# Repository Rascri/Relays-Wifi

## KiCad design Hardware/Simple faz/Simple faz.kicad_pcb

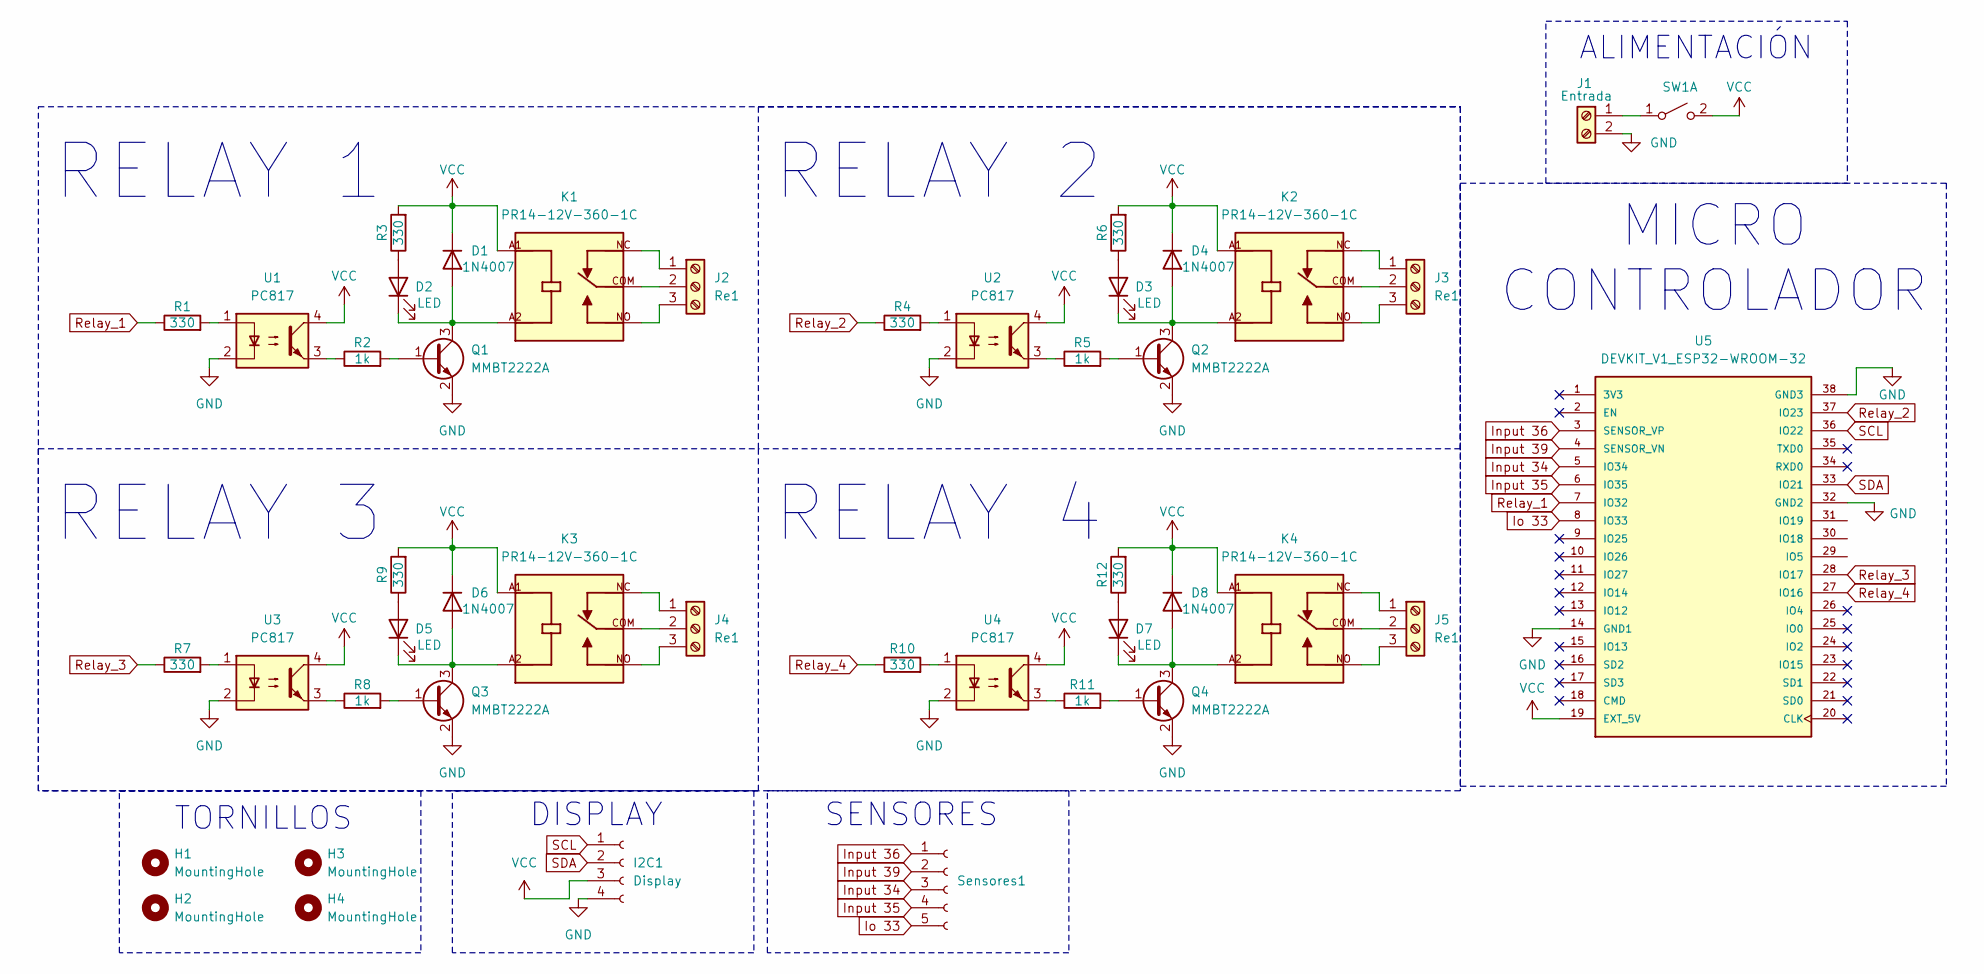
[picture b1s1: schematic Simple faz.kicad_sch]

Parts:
D1, D4, D6, D8: 1N4007; D_SMA
D2, D3, D5, D7: LED; LED_0805_2012Metric
H1, H2, H3, H4: MountingHole; MountingHole_2.5mm
I2C1: Display; PinSocket_1x04_P2.54mm_Vertical
J1: Entrada; TerminalBlock_4Ucon_1x02_P3.50mm_Vertical
J2, J3, J4, J5: Re1; TerminalBlock_4Ucon_1x03_P3.50mm_Vertical
K1, K2, K3, K4: PR14-12V-360-1C; RELAY_PR14-12V-360-1C; PARTREV 1.0
Q1, Q2, Q3, Q4: MMBT2222A; SOT-23
R1, R3, R4, R6, R7, R9, R10, R12: 330; R_0805_2012Metric_Pad1.20x1.40mm_HandSolder
R2, R5, R8, R11: 1k; R_0805_2012Metric_Pad1.20x1.40mm_HandSolder
SW1: PinSocket_1x02_P2.54mm_Vertical
Sensores1: Conn_01x05_Socket; PinSocket_1x05_P2.54mm_Vertical
U1, U2, U3, U4: PC817; SMDIP-4_W7.62mm
U5: DEVKIT_V1_ESP32-WROOM-32; ESP32S; PARTREV N/A

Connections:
GND: I2C1.4, J1.2, Q1.2 (E), Q2.2 (E), Q3.2 (E), Q4.2 (E), U1.2, U2.2, U3.2, U4.2, U5.14 (GND1), U5.32 (GND2), U5.38 (GND3)
Input 34: Sensores1.3, U5.5 (IO34)
Input 35: Sensores1.4, U5.6 (IO35)
Input 36: Sensores1.1, U5.3 (SENSOR_VP)
Input 39: Sensores1.2, U5.4 (SENSOR_VN)
Io 33: Sensores1.5, U5.8 (IO33)
unnamed: D1.2 (A), D2.1 (K), K1.A2, Q1.3 (C)
unnamed: D2.2 (A), R3.1
unnamed: D3.2 (A), R6.1
unnamed: D3.1 (K), D4.2 (A), K2.A2, Q2.3 (C)
unnamed: D5.2 (A), R9.1
unnamed: D5.1 (K), D6.2 (A), K3.A2, Q3.3 (C)
unnamed: D7.2 (A), R12.1
unnamed: D7.1 (K), D8.2 (A), K4.A2, Q4.3 (C)
unnamed: J1.1, SW1.1 (A)
unnamed: J2.1, K1.NC
unnamed: J2.2, K1.COM
unnamed: J2.3, K1.NO
unnamed: J3.1, K2.NC
unnamed: J3.2, K2.COM
unnamed: J3.3, K2.NO
unnamed: J4.1, K3.NC
unnamed: J4.2, K3.COM
unnamed: J4.3, K3.NO
unnamed: J5.1, K4.NC
unnamed: J5.2, K4.COM
unnamed: J5.3, K4.NO
unnamed: Q1.1 (B), R2.2
unnamed: Q2.1 (B), R5.2
unnamed: Q3.1 (B), R8.2
unnamed: Q4.1 (B), R11.2
unnamed: R1.2, U1.1
unnamed: R2.1, U1.3
unnamed: R4.2, U2.1
unnamed: R5.1, U2.3
unnamed: R7.2, U3.1
unnamed: R8.1, U3.3
unnamed: R10.2, U4.1
unnamed: R11.1, U4.3
Relay_1: R1.1, U5.7 (IO32)
Relay_2: R4.1, U5.37 (IO23)
Relay_3: R7.1, U5.28 (IO17)
Relay_4: R10.1, U5.27 (IO16)
SCL: I2C1.1, U5.36 (IO22)
SDA: I2C1.2, U5.33 (IO21)
VCC: D1.1 (K), D4.1 (K), D6.1 (K), D8.1 (K), I2C1.3, K1.A1, K2.A1, K3.A1, K4.A1, R3.2, R6.2, R9.2, R12.2, SW1.2 (B), U1.4, U2.4, U3.4, U4.4, U5.19 (EXT_5V)

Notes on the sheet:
SENSORES
ALIMENTACIÓN
RELAY 4
DISPLAY
RELAY 3
MICRO CONTROLADOR
RELAY 2
RELAY 1
TORNILLOS

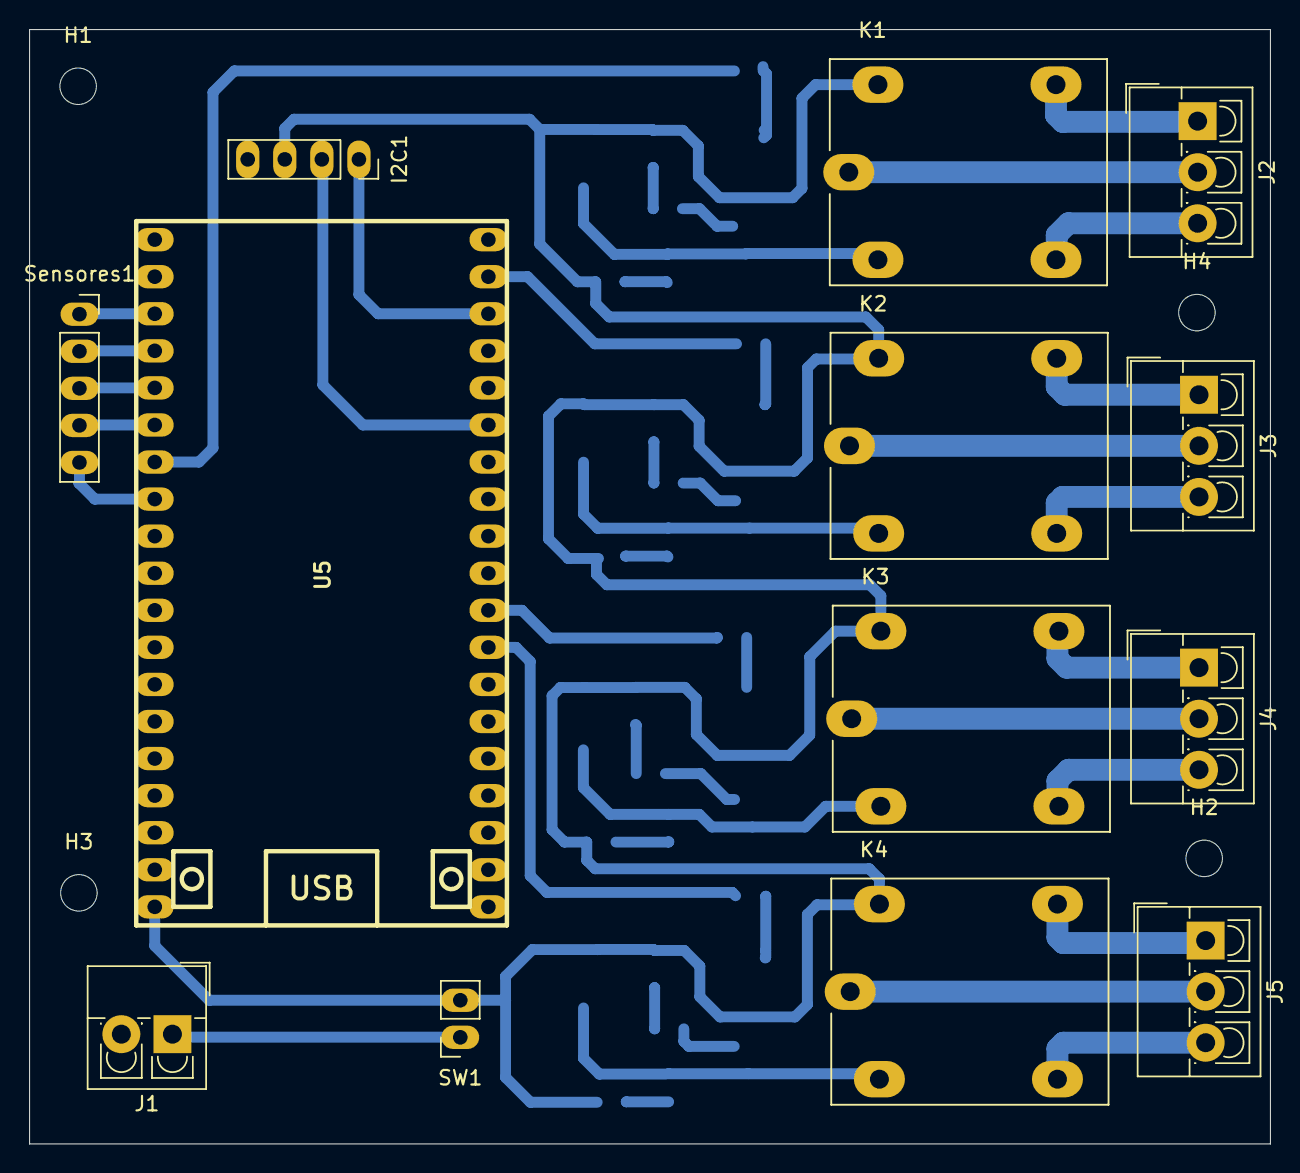
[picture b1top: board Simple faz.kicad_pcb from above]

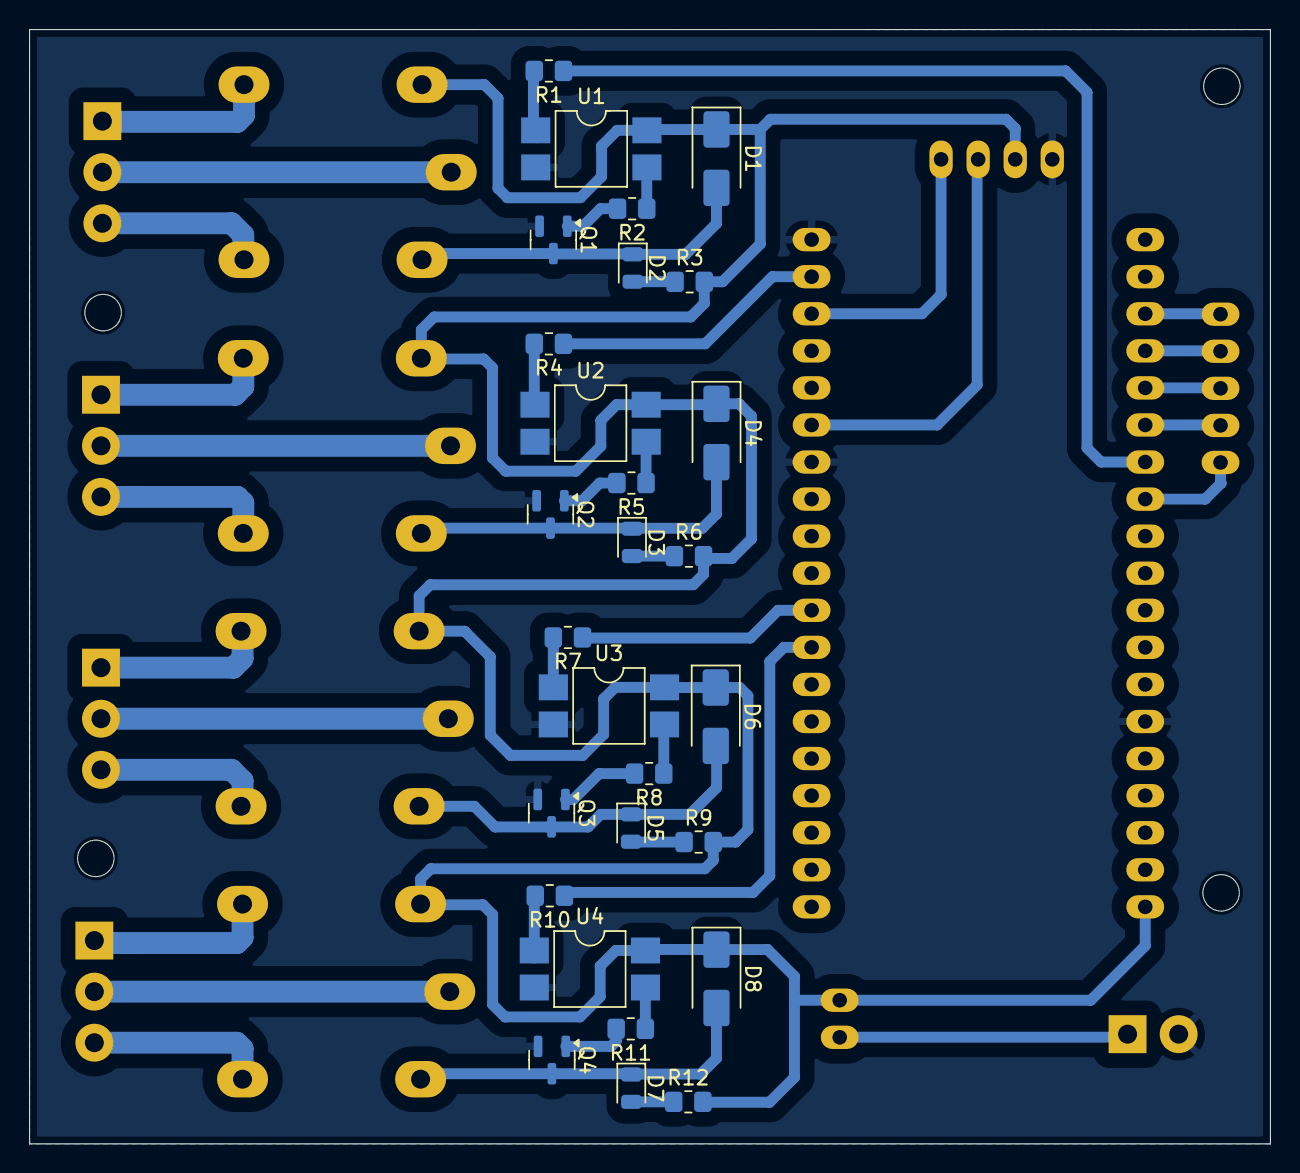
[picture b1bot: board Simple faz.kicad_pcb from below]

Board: 2 copper layers, 85.0 x 76.4 mm, 45 parts (28 on the bottom side), 46 nets.

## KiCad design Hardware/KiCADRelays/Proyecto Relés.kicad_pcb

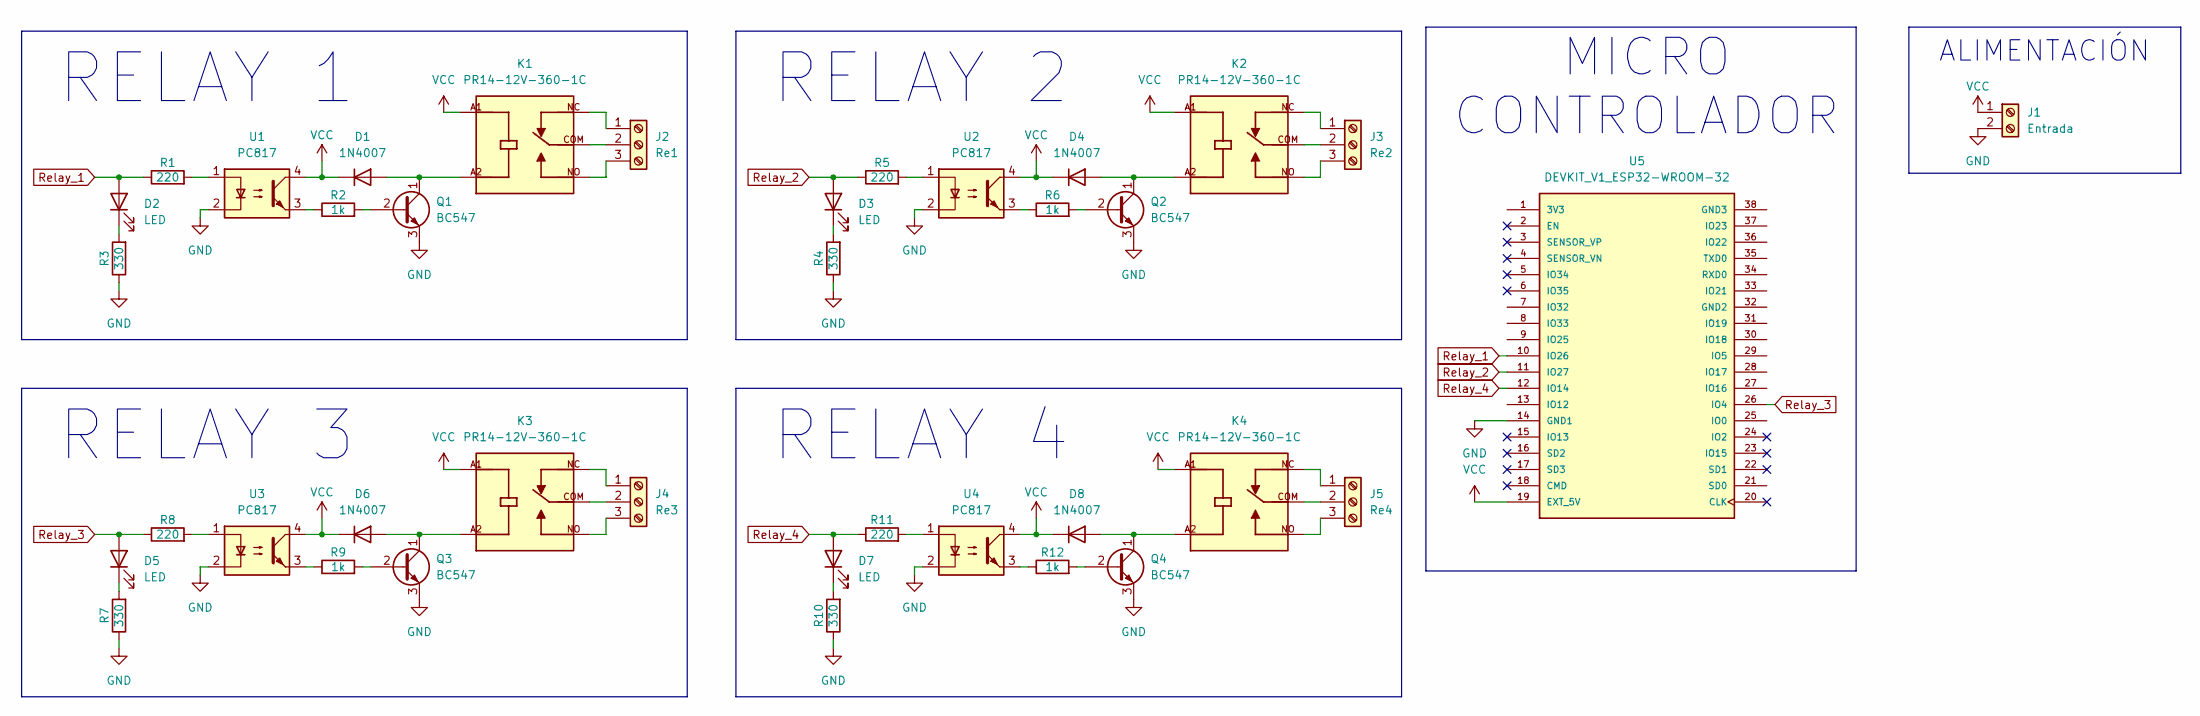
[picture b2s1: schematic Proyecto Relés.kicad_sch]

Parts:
D1, D4, D6, D8: 1N4007; R_0805_2012Metric_Pad1.20x1.40mm_HandSolder
D2, D3, D5, D7: LED; R_0805_2012Metric_Pad1.20x1.40mm_HandSolder
J1: Entrada; TerminalBlock_4Ucon_1x02_P3.50mm_Vertical
J2: Re1; TerminalBlock_4Ucon_1x03_P3.50mm_Vertical
J3: Re2; TerminalBlock_4Ucon_1x03_P3.50mm_Vertical
J4: Re3; TerminalBlock_4Ucon_1x03_P3.50mm_Vertical
J5: Re4; TerminalBlock_4Ucon_1x03_P3.50mm_Vertical
K1, K2, K3, K4: PR14-12V-360-1C; RELAY_PR14-12V-360-1C; PARTREV 1.0
Q1, Q2, Q3, Q4: BC547; TO-92_Inline
R1, R5, R8, R11: 220; R_0805_2012Metric_Pad1.20x1.40mm_HandSolder
R2, R6, R9, R12: 1k; R_0805_2012Metric_Pad1.20x1.40mm_HandSolder
R3, R4, R7, R10: 330; R_0805_2012Metric_Pad1.20x1.40mm_HandSolder
U1, U2, U3, U4: PC817; DIP-4_W7.62mm
U5: DEVKIT_V1_ESP32-WROOM-32; MODULE_DEVKIT_V1_ESP32-WROOM-32; PARTREV N/A

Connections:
GND: J1.2, Q1.3 (E), Q2.3 (E), Q3.3 (E), Q4.3 (E), R3.1, R4.1, R7.1, R10.1, U1.2, U2.2, U3.2, U4.2, U5.14 (GND1)
unnamed: D1.2 (A), K1.A2, Q1.1 (C)
unnamed: D2.1 (K), R3.2
unnamed: D3.1 (K), R4.2
unnamed: D4.2 (A), K2.A2, Q2.1 (C)
unnamed: D5.1 (K), R7.2
unnamed: D6.2 (A), K3.A2, Q3.1 (C)
unnamed: D7.1 (K), R10.2
unnamed: D8.2 (A), K4.A2, Q4.1 (C)
unnamed: J2.1, K1.NC
unnamed: J2.2, K1.COM
unnamed: J2.3, K1.NO
unnamed: J3.1, K2.NC
unnamed: J3.2, K2.COM
unnamed: J3.3, K2.NO
unnamed: J4.1, K3.NC
unnamed: J4.2, K3.COM
unnamed: J4.3, K3.NO
unnamed: J5.1, K4.NC
unnamed: J5.2, K4.COM
unnamed: J5.3, K4.NO
unnamed: Q1.2 (B), R2.2
unnamed: Q2.2 (B), R6.2
unnamed: Q3.2 (B), R9.2
unnamed: Q4.2 (B), R12.2
unnamed: R1.2, U1.1
unnamed: R2.1, U1.3
unnamed: R5.2, U2.1
unnamed: R6.1, U2.3
unnamed: R8.2, U3.1
unnamed: R9.1, U3.3
unnamed: R11.2, U4.1
unnamed: R12.1, U4.3
Relay_1: D2.2 (A), R1.1, U5.10 (IO26)
Relay_2: D3.2 (A), R5.1, U5.11 (IO27)
Relay_3: D5.2 (A), R8.1, U5.26 (IO4)
Relay_4: D7.2 (A), R11.1, U5.12 (IO14)
VCC: D1.1 (K), D4.1 (K), D6.1 (K), D8.1 (K), J1.1, K1.A1, K2.A1, K3.A1, K4.A1, U1.4, U2.4, U3.4, U4.4, U5.19 (EXT_5V)

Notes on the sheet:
ALIMENTACIÓN
RELAY 3
RELAY 1
RELAY 4
MICRO CONTROLADOR
RELAY 2

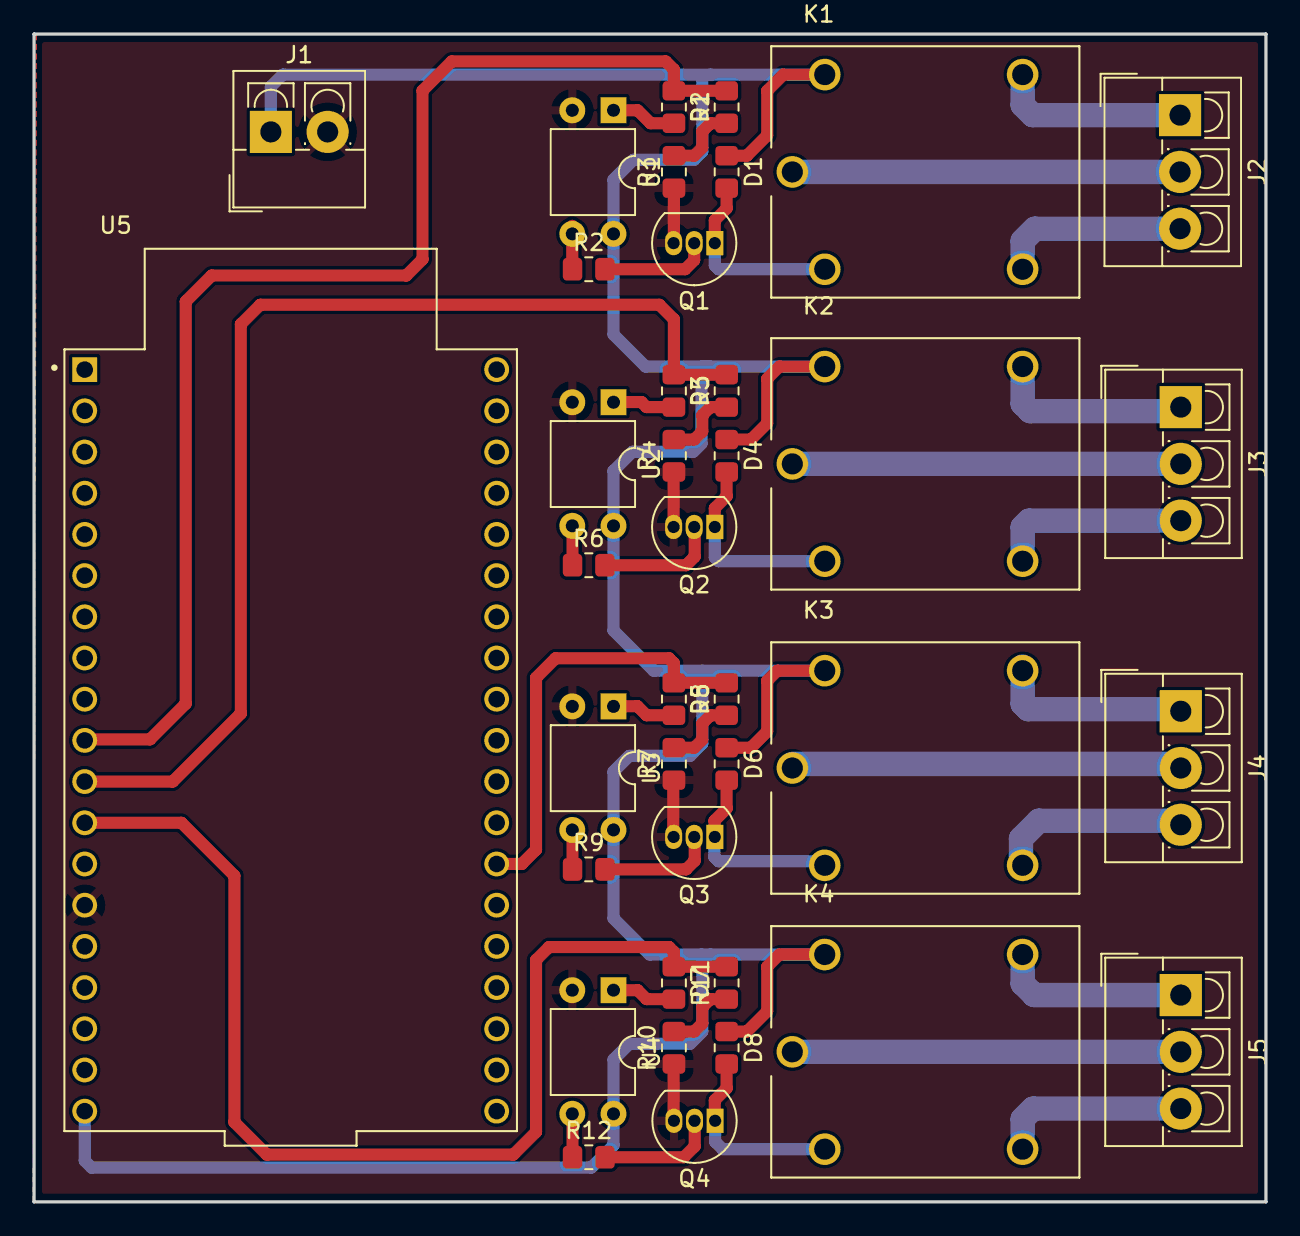
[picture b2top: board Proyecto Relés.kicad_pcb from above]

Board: 2 copper layers, 76.0 x 72.0 mm, 38 parts (0 on the bottom side), 38 nets.

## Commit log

2025-05-04 Primer commit: Subo Hardware, Software y 3D
2025-06-16 Version Final
2025-06-25 Ultima Versión
2025-06-25 Version final 1.0
2025-11-28 Ultima version
